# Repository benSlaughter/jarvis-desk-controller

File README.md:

# Jarvis Desk Controller

Control a Jarvis/Jiecang standing desk via the **RJ-12 port** using the reverse-engineered serial protocol from [phord/Jarvis](https://github.com/phord/Jarvis).

Two platforms are supported:

| Platform | Interface | Features |
|----------|-----------|----------|
| **Arduino Uno** | USB Serial CLI | Direct serial commands, interactive terminal |
| **ESP32-C6** | WiFi + MQTT | Home Assistant auto-discovery, OTA updates |

## Hardware Required

### Arduino Uno
- Arduino Uno
- RJ-12 breakout / socket
- 2× 1kΩ resistors (signal protection)
- Hookup wire

### ESP32-C6
- DFRobot Beetle ESP32-C6 (or any ESP32-C6 board)
- RJ-12 breakout / socket
- 1× 1kΩ + 1× 2kΩ resistor (voltage divider for RX line)
- Hookup wire

## Wiring

The RJ-12 port is the 6-pin telephone-style jack on the desk controller (used for the optional Bluetooth add-on). Only the center 4 pins are needed.

```
 RJ-12 Jack (front view, tab down)
 ┌──────────┐
 │ 1 2 3 4 5 6 │
 └──┬─┬─┬─┬─┬─┬──┘
    │ │ │ │ │ │
    NC│ │ │ │ NC
      │ │ │ │
      │ │ │ └── Pin 5: HTX (to desk) ──[1kΩ]── Arduino Pin 3
      │ │ └──── Pin 4: VCC (5V out)    (see power notes below)
      │ └────── Pin 3: DTX (from desk) ──[1kΩ]── Arduino Pin 2
      └──────── Pin 2: GND ──────────── Arduino GND
```

### Connections Summary

| RJ-12 Pin | Label | Arduino Uno    | Notes                       |
|-----------|-------|----------------|-----------------------------|
| 1         | NC    | —              | Not connected               |
| 2         | GND   | GND            | Common ground (REQUIRED)    |
| 3         | DTX   | Pin 2 (RX)     | Via 1kΩ series resistor     |
| 4         | VCC   | —              | 5V from desk (see below)    |
| 5         | HTX   | Pin 3 (TX)     | Via 1kΩ series resistor     |
| 6         | NC    | —              | Not connected               |

### Why series resistors?

The 1kΩ resistors protect both the Arduino and the desk controller from shorts, voltage spikes during hot-plugging, and current surges. They don't affect signal integrity at 9600 baud.

### Power Options

**For development (recommended):** Power the Arduino via USB. Leave RJ-12 Pin 4 (VCC) disconnected.

**For standalone deployment:** You *can* power the Arduino from the desk's 5V supply on RJ-12 Pin 4 → Arduino 5V pin. However:

> ⚠️ **Never connect both USB and desk 5V simultaneously** — this back-powers the USB host and can damage your computer or the desk controller. Use a diode or power switch if you need both.

### ESP32-C6 Wiring (Desk-Powered)

The ESP32 can be powered directly from the desk's 5V supply — no USB needed
after the first firmware upload (use OTA for updates).

```
                    DFRobot Beetle ESP32-C6
                    ┌─────────────────────┐
                    │                     │
RJ-12              │  VIN ←── 5V power   │
┌──────┐           │  GND ←── Ground     │
│1    6│           │                     │
│ NC  NC│           │  GPIO17 (RX) ←─┐   │
│      │           │                 │   │
│2 GND─┼──────────→│  GND            │   │
│      │           │                 │   │
│3 DTX─┼──[1kΩ]──┬─┼─────────────────┘   │
│      │         │ │                     │
│      │       [2kΩ]                     │
│      │         │ │                     │
│      │        GND│                     │
│      │           │                     │
│4 VCC─┼──────────→│  VIN (5V)           │
│      │           │                     │
│5 HTX─┼──────────→│  GPIO18 (TX)        │
│      │           │                     │
│6  NC │           └─────────────────────┘
└──────┘
```

| RJ-12 Pin | Label | ESP32-C6 | Notes |
|-----------|-------|----------|-------|
| 2 | GND | GND | Common ground (REQUIRED) |
| 3 | DTX | GPIO17 (RX) | Via 1kΩ + 2kΩ voltage divider |
| 4 | VCC | VIN (5V) | Powers the ESP32 from desk |
| 5 | HTX | GPIO18 (TX) | Direct connection — 3.3V is fine |

**Parts needed:** 1× 1kΩ resistor, 1× 2kΩ resistor (or 2× 1kΩ in series)

#### Why the Voltage Divider?

The desk sends data at **5V**. The ESP32-C6 GPIOs are rated for **3.3V max**.
Without a divider, 5V goes straight into a 3.3V pin — this will damage the chip.

Two resistors drop the voltage: `5V × 2kΩ / (1kΩ + 2kΩ) = 3.33V` ✅

The TX line (ESP32→desk) doesn't need this because the ESP32 outputs 3.3V,
which the desk's 5V logic reads as HIGH (above the ~2.5V threshold).

> ⚠️ **Never connect USB and desk 5V at the same time** — this back-powers
> the USB host. Disconnect the RJ-12 before plugging in USB, or use OTA
> for all updates after the first upload.
>
> **Current budget:** The desk provides ~300mA at 5V. The ESP32-C6 draws
> ~120-180mA during WiFi activity — well within budget.

## Serial Signal Notes

Live testing on a Jiecang JCB36N2CA (Fully Jarvis) confirmed **normal UART polarity** — standard 9600/8N1 with no inversion needed. Earlier documentation suggested inverted logic, but this was not the case on the tested controller.

The code uses `SoftwareSerial` with `inverse_logic = false` (standard polarity). If you get garbage data, try toggling this flag — some controller models may differ.

## Building & Uploading (PlatformIO)

This project uses [PlatformIO](https://platformio.org/) for build/upload/serial monitoring.

### Setup

1. Install the **PlatformIO IDE** extension in VSCode (`platformio.platformio-ide`)
2. Open this folder in VSCode — PlatformIO detects `platformio.ini` automatically

### Build, Upload & Monitor

Use the PlatformIO toolbar at the bottom of VSCode, or:

```bash
# Arduino Uno
pio run -e uno
pio run -e uno --target upload

# ESP32-C6
pio run -e esp32c6
pio run -e esp32c6 --target upload

# Tests
pio test -e native

# Open serial monitor (115200 baud)
pio device monitor

# Build + upload + monitor in one shot
pio run -e uno --target upload && pio device monitor
```

### ESP32-C6 Setup

1. Copy `include/config.example.h` to `include/config.h`
2. Edit `config.h` with your WiFi SSID/password and MQTT broker IP
3. Build: `pio run -e esp32c6`
4. Upload: `pio run -e esp32c6 --target upload`
5. Monitor: `pio device monitor`

### Home Assistant Integration

The ESP32 firmware publishes MQTT auto-discovery messages. After connecting:

- A **"Jarvis Desk"** device appears automatically in Home Assistant
- **Entities:** height sensor (cm), target height (number), presets 1–4 (buttons), up/down/stop (buttons)
- **Requires** an MQTT broker (e.g., Mosquitto) configured in Home Assistant

### MQTT Topics

| Topic | Direction | Description |
|-------|-----------|-------------|
| `jarvis-desk/status` | ESP→broker | Online/offline status (retained LWT) |
| `jarvis-desk/height/state` | ESP→broker | Current height in mm (retained) |
| `jarvis-desk/height/set` | broker→ESP | Move to target height in mm |
| `jarvis-desk/preset/set` | broker→ESP | Move to preset (payload: `1`–`4`) |
| `jarvis-desk/command` | broker→ESP | Send command: `up`, `down`, `stop` |
| `jarvis-desk/collision/set` | broker→ESP | Set collision sensitivity: `high`, `medium`, `low` |

### OTA Updates

After the first upload via USB, subsequent updates can use OTA:

```bash
pio run -e esp32c6 --target upload --upload-port jarvis-desk.local
```

### Alternative: Arduino IDE

If you prefer the Arduino IDE, copy files from `src/` and `include/` into a single
folder named `jarvis-desk-controller/`, rename `main.cpp` → `jarvis-desk-controller.ino`,
and open it in the Arduino IDE.

## Usage

Open the Serial Monitor at **115200 baud**. Type commands and press Enter:

| Command       | Action                         |
|---------------|--------------------------------|
| `up` / `raise`| Raise desk one step            |
| `down`/`lower`| Lower desk one step            |
| `1` `2` `3` `4`| Move to memory preset        |
| `save1`..`save4`| Save current height to preset|
| `height`      | Request current height         |
| `settings`    | Request all desk settings      |
| `limits`      | Request min/max limits         |
| `wake`        | Send wake signal               |
| `cm` / `in`   | Set display units              |
| `status`      | Show connection state          |
| `help`        | List all commands              |

### What you'll see

```
=== Jarvis Desk Controller ===
Type 'help' for commands

Waking desk...
[DESK] HEIGHT (05 06 07)  height=1286
> Moving to preset 1
[DESK] HEIGHT (03 CA 07)  height=970
```

## Protocol Reference

- **UART:** 9600 baud, 8N1, normal polarity (not inverted)
- **Packets:** `[addr][addr][cmd][len][params...][checksum][0x7E]`
- **Handset address:** `0xF1 0xF1`
- **Controller address:** `0xF2 0xF2`
- **Checksum:** Low byte of `(cmd + len + params...)`, i.e. `& 0xFF`

Full protocol documentation: https://github.com/phord/Jarvis

## Protocol Discoveries (Live Testing)

Tested on a **Jiecang JCB36N2CA** (Fully Jarvis, RJ-12 port). The RJ-12 interface works standalone — no handset required.

### Confirmed Commands (Handset → Desk)

| Cmd  | Name       | Params     | Response                  | Notes                                              |
|------|------------|------------|---------------------------|----------------------------------------------------|
| 0x01 | RAISE      | 0          | HEIGHT stream             | Continuous raise when sent repeatedly              |
| 0x02 | LOWER      | 0          | HEIGHT stream             | Continuous lower when sent repeatedly              |
| 0x05 | MOVE_1     | 0          | HEIGHT stream             | Moves to preset 1, auto-stops                      |
| 0x06 | MOVE_2     | 0          | HEIGHT stream             | Moves to preset 2, auto-stops                      |
| 0x07 | SETTINGS   | 0          | POS_1–4 + HEIGHT          | Returns all 4 presets and current height            |
| 0x0C | PHYS_LIMITS| 0          | 0x07 (HI HI LO LO)       | Physical motion limits: max/min in mm              |
| 0x1B | GOTO_HEIGHT| 2 (HI, LO)| 0x1B echo + HEIGHT stream | **Native goto-height.** Desk handles accel/decel/stop |
| 0x20 | LIMITS     | 0          | 0x20 (00)                 | User-set limits bitmask. 0x00 = none set           |
| 0x27 | MOVE_3     | 0          | HEIGHT stream             | Moves to preset 3, auto-stops                      |
| 0x28 | MOVE_4     | 0          | HEIGHT stream             | Moves to preset 4, auto-stops                      |
| 0x29 | WAKE       | 0          | none (display only)       | Wakes display. No data response on RJ-12           |
| 0x2B | STOP       | 0          | none                      | Stops all movement immediately                     |

### Controller Responses

| Resp | Name       | Params | Meaning                                               |
|------|------------|--------|-------------------------------------------------------|
| 0x01 | HEIGHT     | 3      | {P0,P1} = height mm, P2 = flags (always 0x0F here)    |
| 0x07 | PHYS_LIMITS| 4      | {P0,P1} = max mm, {P2,P3} = min mm                    |
| 0x1B | GOTO_ACK   | 2      | Echoes target height                                   |
| 0x20 | LIMITS     | 1      | Bitmask of user-set limits                             |
| 0x25–0x28 | POS_1–4 | 2   | Raw encoder value (NOT display mm)                     |

### Key Observations

- **Normal UART polarity** — standard 9600/8N1, no inversion needed.
- **GOTO_HEIGHT (0x1B)** is the cleanest move method — desk handles acceleration, deceleration, and auto-stop.
- **STOP (0x2B)** halts movement immediately. ESPHome uses wake + stop as an init sequence.
- **Preset values** are raw encoder positions, not display millimeters.
- **Height offset:** Display height has a ~2.4 cm offset from physical (tape-measure) height.
- **Physical limits** on tested unit: 76.5–125.3 cm reported, ~74.1–122.9 cm actual.
- **No-response commands:** 0x0E (UNITS), 0x19 (MEM_MODE), 0x1D (COLL_SENS) — these are setters that likely need parameters, or are RJ-45 only.

## RJ-12 vs RJ-45

This project uses the **RJ-12** interface (6-pin, Bluetooth add-on port). The larger **RJ-45** port (8-pin, handset port) has additional button mux lines (HS0-HS3) not available on RJ-12.

On RJ-12, some responses differ:
- `SETTINGS` returns fewer response packets
- `LIMIT_STOP` and `REP_PRESET` are not sent

## Troubleshooting

| Problem | Try |
|---------|-----|
| No response from desk | Check GND connection. Try `wake` command repeatedly. |
| Garbage data | Toggle `inverse_logic` in the SoftwareSerial constructor. Normal polarity (false) confirmed on JCB36N2CA. |
| Partial/corrupt packets | Check series resistors are connected. Reduce Serial.print debug output. |
| Desk doesn't move | The raise/lower commands send a single step. You may need to send repeatedly. |

## License

This project is for personal/educational use. The protocol was reverse-engineered by [phord](https://github.com/phord/Jarvis).

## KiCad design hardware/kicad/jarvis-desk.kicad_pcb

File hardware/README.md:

# Jarvis Desk Controller — Hardware

Custom PCB to connect a DFRobot Beetle ESP32-C6 to a Jarvis standing desk via
the RJ-12 control port. The board provides a voltage divider on the desk→MCU
data line (5 V → 3.3 V logic) and breaks out power + UART signals.

## Bill of Materials

| Ref | Part | Value | Package / Footprint | Qty | Example Part Number |
|-----|------|-------|---------------------|-----|---------------------|
| U1 | DFRobot Beetle ESP32-C6 | — | 2×7 pin header, 2.54 mm pitch | 1 | DFRobot DFR1117 |
| J1 | RJ-12 socket | 6P6C | Through-hole, right-angle | 1 | Amphenol 54601-906LF |
| R1 | Resistor | 1 kΩ | 0805 (or 1/4 W through-hole) | 1 | — |
| R2 | Resistor | 2 kΩ | 0805 (or 1/4 W through-hole) | 1 | — |
| — | Pin headers (female) | 2.54 mm | 1×7, through-hole | 2 | — |

> **Note:** If you use through-hole resistors, increase the board width by a
> few mm to accommodate them.

## Assembly Instructions

### 1. Order the PCB

See [PCB Ordering Guide](#pcb-ordering-guide) below or the detailed
[KiCad Guide](kicad-guide.md) for Gerber generation.

### 2. Solder Components (order matters)

1. **SMD resistors first** (if using 0805) — R1 (1 kΩ) and R2 (2 kΩ). They
   sit on the top side between the RJ-12 footprint and the pin headers.
2. **RJ-12 socket (J1)** — Push through from the top, solder on the bottom.
   The socket opening should face the board edge.
3. **Female pin headers** — Two 1×7 strips for the Beetle. Solder from the
   bottom so the Beetle plugs in on top.
4. **Plug in the Beetle** — The USB-C port should face away from the RJ-12
   socket.

### 3. Connect to Desk

Use a straight-through RJ-12 6P6C cable (all 6 pins wired 1-to-1). Plug one
end into the controller's handset port and the other into J1.

### 4. Flash Firmware

Connect USB-C to the Beetle and flash with PlatformIO:

```bash
pio run -t upload
```

## PCB Ordering Guide

### JLCPCB

1. In KiCad, go to **File → Fabrication Outputs → Gerbers (.gbr)**.
2. Also generate the drill file (Excellon format).
3. Zip all Gerber + drill files together.
4. Go to <https://www.jlcpcb.com/> → **Order Now** → upload the zip.
5. Recommended settings:
   - **Layers:** 2
   - **PCB Thickness:** 1.6 mm
   - **Surface Finish:** HASL (lead-free)
   - **PCB Color:** any (green is cheapest)
   - **Dimensions:** ~35 mm × 25 mm
   - **Qty:** 5 (minimum)
6. Total cost is typically **$2–5 USD** + shipping for 5 boards.

### PCBWay

Same Gerber zip works. Upload at <https://www.pcbway.com/> → **Instant Quote**.
Use the same settings as above.

## Schematic Overview

See [schematic.md](schematic.md) for the full ASCII schematic and component
details.

```
RJ12 Pin 2 (GND) ───────────────── Beetle GND
RJ12 Pin 3 (DTX) ──[R1 1kΩ]──┬── Beetle GPIO17 (RX)
                               │
                            [R2 2kΩ]
                               │
                              GND
RJ12 Pin 4 (VCC) ───────────────── Beetle VIN (5V)
RJ12 Pin 5 (HTX) ───────────────── Beetle GPIO18 (TX)
```

## Files

| File | Description |
|------|-------------|
| [README.md](README.md) | This file — BOM, assembly, ordering |
| [schematic.md](schematic.md) | ASCII schematic and component details |
| [kicad-guide.md](kicad-guide.md) | Step-by-step KiCad PCB design guide |

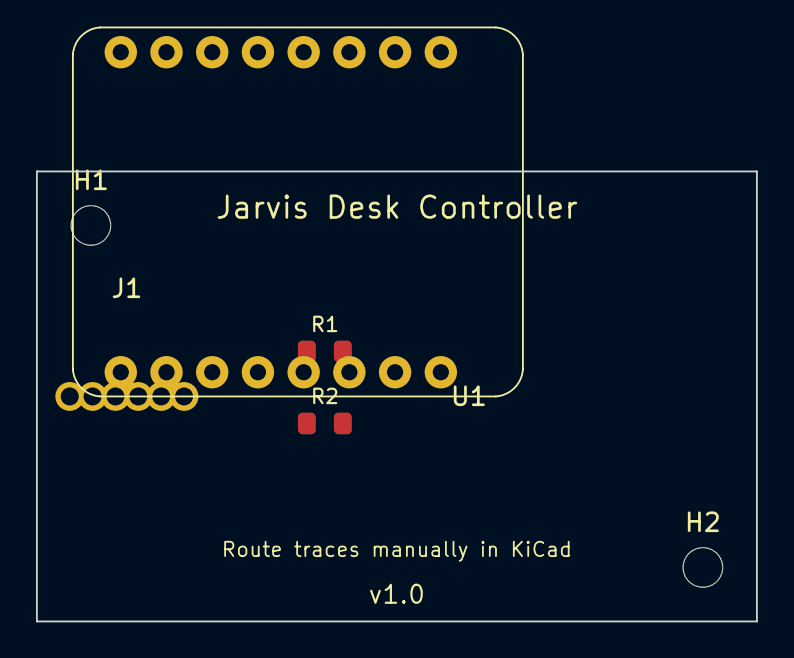
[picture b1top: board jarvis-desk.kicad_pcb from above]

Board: 2 copper layers, 40.0 x 25.0 mm, 6 parts (0 on the bottom side), 5 nets, no tracks yet.

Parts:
H1, H2: MountingHole_M2; MountingHole_2.2mm_M2
J1: RJ12_6P6C; RJ12_Amphenol_54601
R1: 1k; R_0805_2012Metric
R2: 2k; R_0805_2012Metric
U1: Beetle_ESP32-C6

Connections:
DTX: J1.3, R1.1
GND: J1.2, R2.2, U1.1, U1.15
HTX: J1.5, U1.12
RX_DIV: R1.2, R2.1, U1.13
VCC_5V: J1.4, U1.14
